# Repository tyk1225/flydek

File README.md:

# FLYDEK

**A desk control panel for PC flight simulators, with a screen that draws the labels for its keys.**

> Status: The PCB is designed, ordered and tested, the Pico is soldered, and firmware is next!

## What it is

FLYDEK v1 is a control deck that sits on your desk next to the keyboard while you fly. A 4-inch screen sits behind a window cut into the circuit board, with 6 keys above it and 6 keys below it. The keys have no printed labels: the screen draws each key's label right next to it, so the same 12 keys can do different jobs in each sim or aircraft profile.

On the left are two dual knobs (an outer ring and an inner knob, both with a push), for things you turn a lot, like heading and altitude. MASTER WARN and MASTER CAUT buttons with red and orange lights sit in the top-left corner, like in a real cockpit, and PROFILE and MENU buttons are on the right. A plug on the side (J4) is ready for a Lever Pack add-on with a gear lever and a flaps lever.

What makes it different: the labels change on the screen, and the plan is for FLYDEK to show up as a normal USB game controller and keyboard, so it needs no driver.

## How to use it

Firmware v1 is still being written, so this is how v1 is planned to work:

1. **Plug it in:** connect the Pico 2's USB port to your PC. FLYDEK shows up as a game controller and a keyboard.
2. **Pick a profile:** press **PROFILE** to switch between Desktop, Microsoft Flight Simulator and Roblox. The screen redraws all 12 key labels.
3. **Press a key:** each key sends the button or shortcut written next to it on the screen.
4. **Turn the knobs:** the outer ring and the inner knob each send their own inputs (for example heading and altitude), and pushing the knob is a third input.
5. **MENU:** opens settings on the screen (for example brightness).
6. **MASTER WARN / MASTER CAUT:** buttons you can map to your sim's warning controls; their lights are controlled by the firmware.

## How to build it

1. Order the PCB from the Gerbers in this repo (2-layer, 190 × 120 mm).
2. Buy the parts in `BOM.csv`.
3. Solder the low parts first: resistors, capacitors, the 28-pin socket for the MCP23017, then the two 20-pin sockets for the Pico 2, the screen header (J3) and the Lever Pack plug (J4) on the back.
4. Solder the 16 key switches, the 2 knobs and the 2 LEDs on the front.
5. Put the MCP23017 into its socket and the Pico 2 into its sockets.
6. Mount the screen behind the window on 4 mm spacers with M3 × 12 screws, and screw on the 4 × 35 mm brass legs.
7. Flash the firmware: hold BOOTSEL on the Pico 2, plug in USB, and drag the `.uf2` file onto the drive that appears.

## Why I made it

I fly Microsoft Flight Simulator and various flight sims on my PC, and pressing keyboard shortcuts in the middle of a flight breaks the feeling of flying a real plane. Ready-made sim panels I looked at cost about $130–180, and their buttons have fixed labels. My motto is "Don't buy it, make it", so I decided to design my own. FLYDEK started as an idea for a flight stick and turned into this deck. It's also my first real PCB: I wanted to learn how to design a circuit board from scratch, route every track myself and solder it together.

## Hardware (v1)

| Part | v1 |
|---|---|
| Board | 190 × 120 mm, 2-layer, through-hole, designed and routed by hand in KiCad 10 |
| Brain | Raspberry Pi Pico 2 in two 20-pin sockets on the back |
| Screen | 4.0" 480 × 320 SPI TFT (ST7796S, no touch), behind a window in the board |
| Keys | 16 × Omron B3F-4055: 12 softkeys around the screen, PROFILE, MENU, MASTER WARN, MASTER CAUT |
| Key reading | MCP23017 I/O expander (I2C) for the softkeys, PROFILE and MENU; WARN/CAUT on the Pico |
| Knobs | 2 × Bourns PEC11D dual concentric encoders with push |
| Lights | 2 × 3 mm LEDs (red WARN, orange CAUT) |
| Add-on port | J4 (JST XH 8-pin): gear up/off/down + I2C for the Lever Pack |
| Mounting | 4 × 35 mm brass M3 legs; screen on 4 mm spacers with M3 × 12 screws |

## Files

- KiCad project and Gerbers: this repo
- 3D model: `cad/FLYDEK-v1.step`
- Render: `images/FLYDEK-v1.png`
- Parts list with links and prices: `BOM.csv` (about $104 for one board)

## Status

- [x] Schematic and PCB designed in KiCad 10 (routed by hand)
- [x] 5 PCBs made by JLCPCB, beep-tested (17 Nov)
- [x] Pico 2 headers soldered and checked for shorts (20–21 Nov)
- [x] STEP with every 3D model
- [x] Screen arrives (in customs, 22 Nov)
- [ ] Firmware v1: USB game controller + key labels on the screen
- [ ] Remaining parts, then solder and test the full board
- [ ] Lever Pack (subproject)

## Where FLYDEK is going (V4, later)

- My own RP2350B board instead of the Pico 2!
- Backlit black PCB faceplate and RGB light
- Lever Pack: spring-locked gear lever, clicking flaps lever
- Two screen themes (A-style and B-style)
- Web configurator for profiles and key labels
- Live sim data through MobiFlight

## AI use
Claude AI was used for research, 3d rendering, README stems, firmware examples, error fixes, file management, and debugging

## Not affiliated

FLYDEK is an independent project. It is not made by or affiliated with Microsoft, Laminar Research, Boeing or Airbus. "Works with" mentions only describe compatibility.

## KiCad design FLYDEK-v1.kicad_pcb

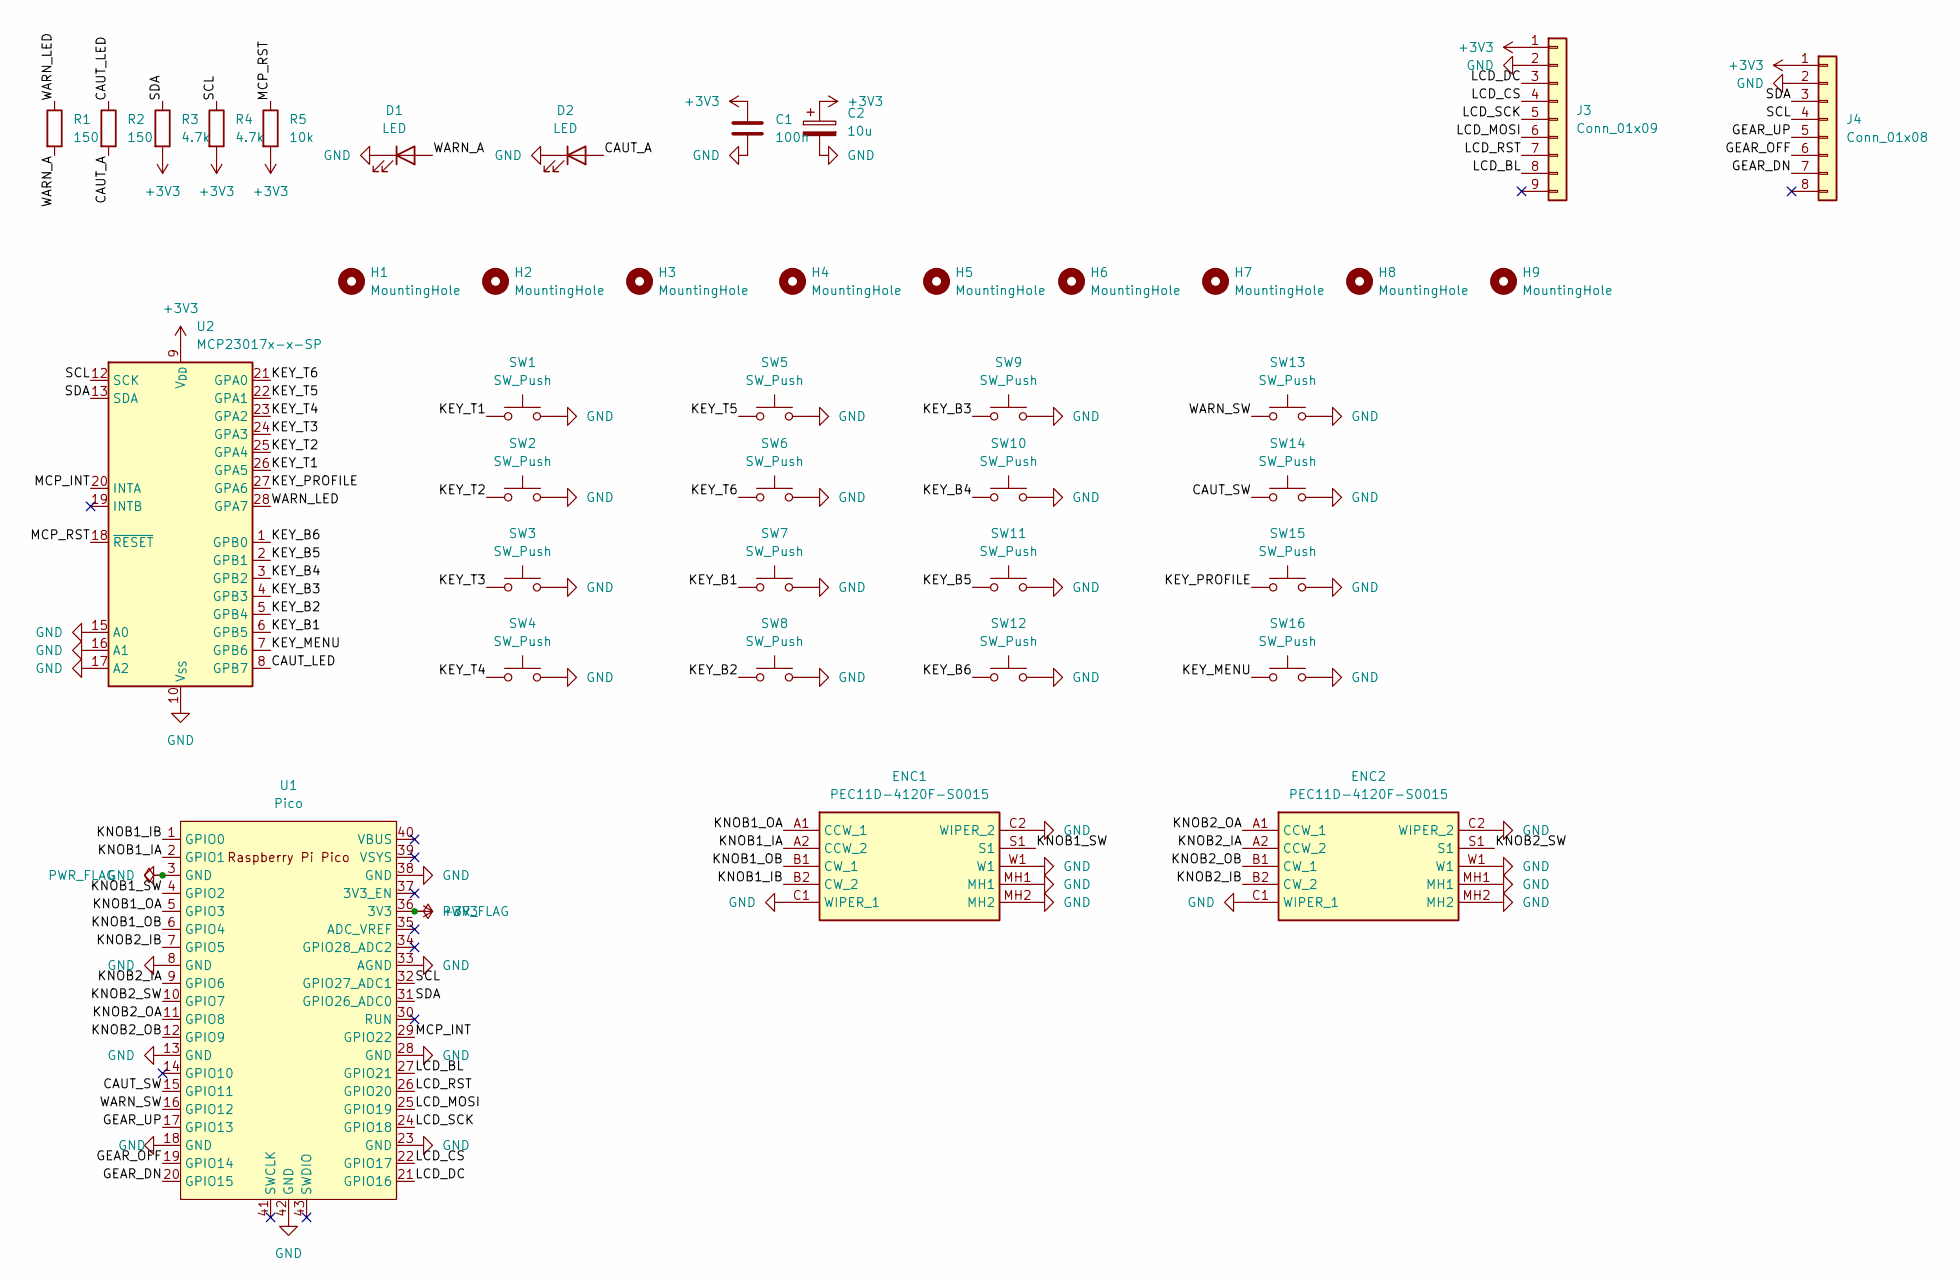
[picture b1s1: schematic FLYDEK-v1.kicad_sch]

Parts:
C1: 100n; C_Disc_D5.0mm_W2.5mm_P5.00mm
C2: 10u; CP_Radial_D5.0mm_P2.00mm
D1, D2: LED; LED_D3.0mm
ENC1, ENC2: PEC11D-4120F-S0015; PEC11D4120FS0015; Manufacturer_Part_Number PEC11D-4120F-S0015
H1, H2, H3, H4, H5, H6, H7, H8, H9: MountingHole; MountingHole_3.2mm_M3
J3: Conn_01x09; PinHeader_1x09_P2.54mm_Vertical
J4: Conn_01x08; JST_XH_S8B-XH-A_1x08_P2.50mm_Horizontal
R1, R2: 150; R_Axial_DIN0207_L6.3mm_D2.5mm_P10.16mm_Horizontal
R3, R4: 4.7k; R_Axial_DIN0207_L6.3mm_D2.5mm_P10.16mm_Horizontal
R5: 10k; R_Axial_DIN0207_L6.3mm_D2.5mm_P10.16mm_Horizontal
SW1, SW2, SW3, SW4, SW5, SW6, SW7, SW8, SW9, SW10, SW11, SW12, SW13, SW14, SW15, SW16: SW_Push; SW_PUSH-12mm
U1: Pico; RPi_Pico_SMD_TH
U2: MCP23017x-x-SP; DIP-28_W7.62mm

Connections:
+3V3: C1.1, C2.1, J3.1, J4.1, R3.2, R4.2, R5.2, U1.36 (3V3), U2.9 (V_{DD})
/CAUT_A: D2.2 (A), R2.2
/CAUT_LED: R2.1, U2.8 (GPB7)
/CAUT_SW: SW14.1, U1.15 (GPIO11)
/GEAR_DN: J4.7, U1.20 (GPIO15)
/GEAR_OFF: J4.6, U1.19 (GPIO14)
/GEAR_UP: J4.5, U1.17 (GPIO13)
/KEY_B1: SW7.1, U2.6 (GPB5)
/KEY_B2: SW8.1, U2.5 (GPB4)
/KEY_B3: SW9.1, U2.4 (GPB3)
/KEY_B4: SW10.1, U2.3 (GPB2)
/KEY_B5: SW11.1, U2.2 (GPB1)
/KEY_B6: SW12.1, U2.1 (GPB0)
/KEY_MENU: SW16.1, U2.7 (GPB6)
/KEY_PROFILE: SW15.1, U2.27 (GPA6)
/KEY_T1: SW1.1, U2.26 (GPA5)
/KEY_T2: SW2.1, U2.25 (GPA4)
/KEY_T3: SW3.1, U2.24 (GPA3)
/KEY_T4: SW4.1, U2.23 (GPA2)
/KEY_T5: SW5.1, U2.22 (GPA1)
/KEY_T6: SW6.1, U2.21 (GPA0)
/KNOB1_IA: ENC1.A2 (CCW_2), U1.2 (GPIO1)
/KNOB1_IB: ENC1.B2 (CW_2), U1.1 (GPIO0)
/KNOB1_OA: ENC1.A1 (CCW_1), U1.5 (GPIO3)
/KNOB1_OB: ENC1.B1 (CW_1), U1.6 (GPIO4)
/KNOB1_SW: ENC1.S1, U1.4 (GPIO2)
/KNOB2_IA: ENC2.A2 (CCW_2), U1.9 (GPIO6)
/KNOB2_IB: ENC2.B2 (CW_2), U1.7 (GPIO5)
/KNOB2_OA: ENC2.A1 (CCW_1), U1.11 (GPIO8)
/KNOB2_OB: ENC2.B1 (CW_1), U1.12 (GPIO9)
/KNOB2_SW: ENC2.S1, U1.10 (GPIO7)
/LCD_BL: J3.8, U1.27 (GPIO21)
/LCD_CS: J3.4, U1.22 (GPIO17)
/LCD_DC: J3.3, U1.21 (GPIO16)
/LCD_MOSI: J3.6, U1.25 (GPIO19)
/LCD_RST: J3.7, U1.26 (GPIO20)
/LCD_SCK: J3.5, U1.24 (GPIO18)
/MCP_INT: U1.29 (GPIO22), U2.20 (INTA)
/MCP_RST: R5.1, U2.18 (~RESET)
/SCL: J4.4, R4.1, U1.32 (GPIO27_ADC1), U2.12 (SCK)
/SDA: J4.3, R3.1, U1.31 (GPIO26_ADC0), U2.13 (SDA)
/WARN_A: D1.2 (A), R1.2
/WARN_LED: R1.1, U2.28 (GPA7)
/WARN_SW: SW13.1, U1.16 (GPIO12)
GND: C1.2, C2.2, D1.1 (K), D2.1 (K), ENC1.C1 (WIPER_1), ENC1.C2 (WIPER_2), ENC1.MH1, ENC1.MH2, ENC1.W1, ENC2.C1 (WIPER_1), ENC2.C2 (WIPER_2), ENC2.MH1, ENC2.MH2, ENC2.W1, J3.2, J4.2, SW1.2, SW2.2, SW3.2, SW4.2, SW5.2, SW6.2, SW7.2, SW8.2, SW9.2, SW10.2, SW11.2, SW12.2, SW13.2, SW14.2, SW15.2, SW16.2, U1.3 (GND), U1.8 (GND), U1.13 (GND), U1.18 (GND), U1.23 (GND), U1.28 (GND), U1.33 (AGND), U1.38 (GND), U1.42 (GND), U2.10 (V_{SS}), U2.15 (A0), U2.16 (A1), U2.17 (A2)

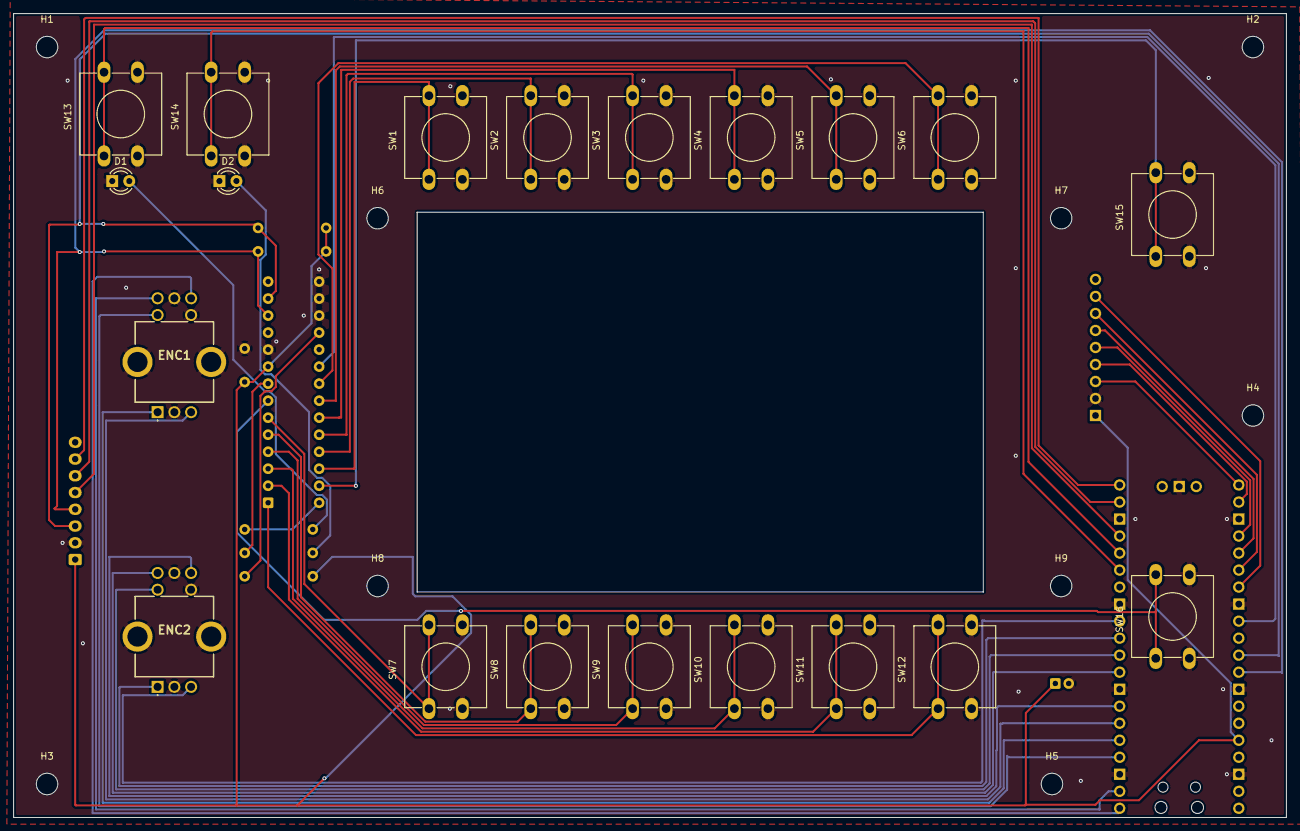
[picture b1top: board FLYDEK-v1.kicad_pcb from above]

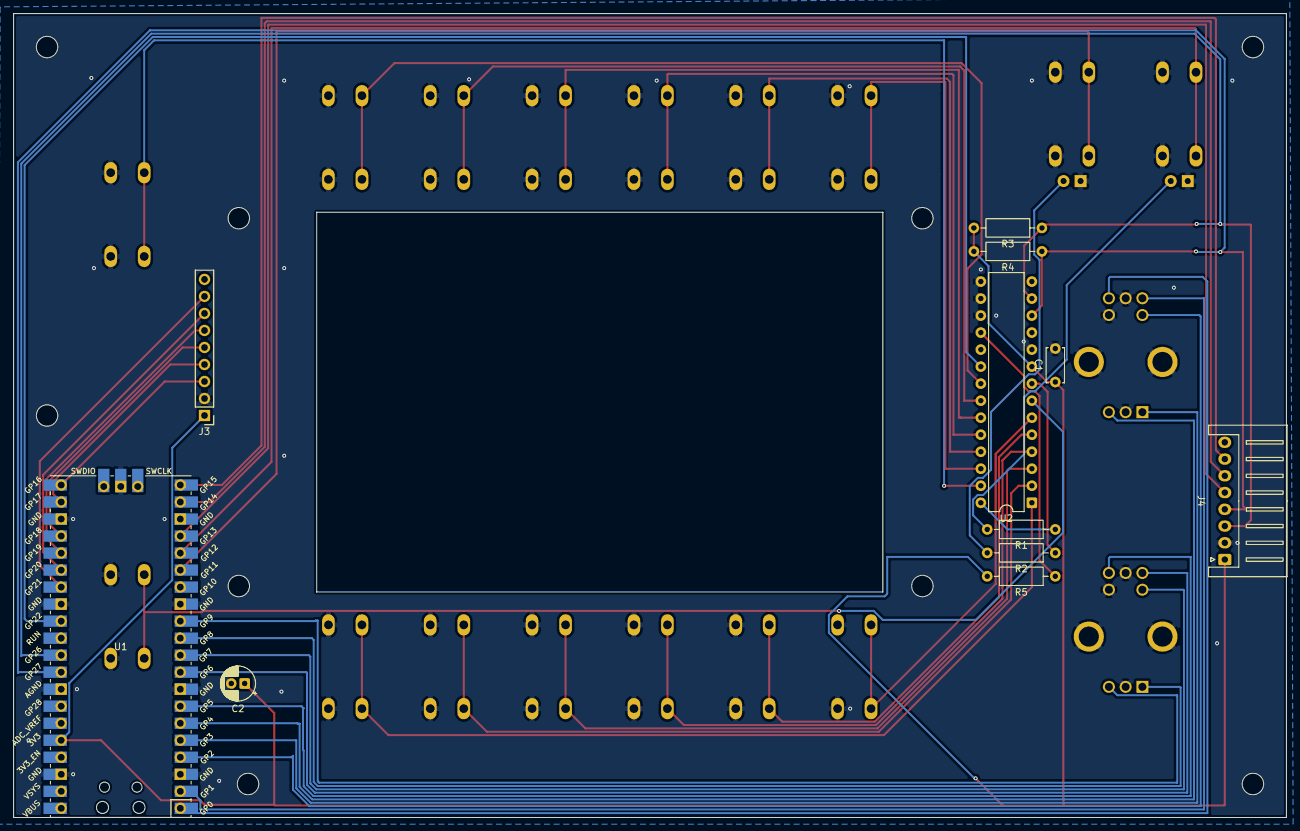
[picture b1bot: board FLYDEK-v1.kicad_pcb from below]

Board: 2 copper layers, 190.0 x 120.0 mm, 40 parts (11 on the bottom side), 45 nets.
